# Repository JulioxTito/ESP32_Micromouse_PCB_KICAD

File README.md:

# ESP32-S3 Micromouse Robot Controller

A compact robotics breakout and control PCB designed for an autonomous maze-solving Micromouse robot. The board integrates power regulation, dual distance sensor interfaces, and motor driver breakouts around an ESP32-S3 system.

## Features

- **ESP32-S3 Core Module**
  - Surface-mount ESP32-S3-WROOM-1 footprint with dedicated antenna keep-out area
  - Native USB D+/D- lines routed to GPIO 19 and 20 for firmware flashing and debugging

- **Dual I2C Distance Sensor Breakouts**
  - Dual 4-pin headers (J3, J4) for left and right Time-of-Flight / IR obstacle sensors
  - Integrated 4.7k pull-up resistors on SDA and SCL lines

- **Dual DC Motor Driver Interface**
  - 6-pin header (J2) providing 5V, GND, dual PWM speed channels, and direction pins for an external H-bridge

- **USB-C Power Input & 3.3V Regulation**
  - 16-pin USB Type-C receptacle with dual 5.1k CC pull-down resistors for standard 5V supply
  - Onboard AMS1117-3.3 linear regulator with 10uF input/output ceramic filtering capacitors

- **Hardware Control Switches**
  - Tactile pushbuttons for RESET and BOOT mode selection with RC filtering and pull-ups

- **Chassis Mounting**
  - 4x M2.5 screw mounting holes with dedicated copper clearance for robot mechanical framing

## Schematic & Layout

Schematic:

[Download Schematic PDF](Media/esp32_micromouse_schematic.pdf)

PCB Layout:

## Skills Demonstrated

- KiCad 10 schematic capture and 2-layer PCB layout routing
- Complete Design Rule Check (DRC) verification with 0 errors and 0 parity warnings
- SMT footprint routing (ESP32-S3, USB-C, 0805 passives, SOT-223)
- Continuous ground plane flooding and thermal relief connections
- Functional silkscreen documentation with circuit grouping outlines and header pinouts
- Fabrication data generation (RS-274X Gerbers, Excellon NC drill files)

## Key Components & Footprints

| Designator | Component | Footprint / Package | Function |
| :--- | :--- | :--- | :--- |
| U1 | AMS1117-3.3 | SOT-223 | 5V to 3.3V LDO regulator |
| U2 | ESP32-S3-WROOM-1 | SMD Module | Main system microcontroller |
| J1 | USB-C Receptacle | 16-Pin SMD | 5V power and USB data |
| J2 | Pin Header 1x06 | 2.54 mm Pitch TH | Motor driver interface |
| J3, J4 | Pin Header 1x04 | 2.54 mm Pitch TH | Left and right I2C distance sensors |
| SW1, SW2 | Tactile Switch | 6x6 mm Pushbutton | RESET and BOOT triggers |
| R1, R2 | 5.1k Resistor | 0805 SMD | USB-C CC line pull-downs |
| R3, R4 | 10k Resistor | 0805 SMD | EN and BOOT pull-up network |
| R5, R6 | 4.7k Resistor | 0805 SMD | I2C SDA and SCL bus pull-ups |
| C1, C2 | 10uF Capacitor | 0805 SMD | LDO input and output decoupling |
| C3, C4 | 0.1uF / 1uF Capacitor | 0805 SMD | Power rail filtering and reset debounce |

## File Formats

- Hardware_Files/ contains editable KiCad project, schematic, and board layout files
- Gerbers_Micromouse_v1.0.zip contains generated fabrication Gerber and drill files for PCB manufacturing
- 3D Models/ contains component 3D step and wrl models used for rendering
- Media/ contains board layouts, schematic exports, and 3D renders

## Author

Julio Tito  
Rutgers University – New Brunswick  
B.S. in Electrical and Computer Engineering

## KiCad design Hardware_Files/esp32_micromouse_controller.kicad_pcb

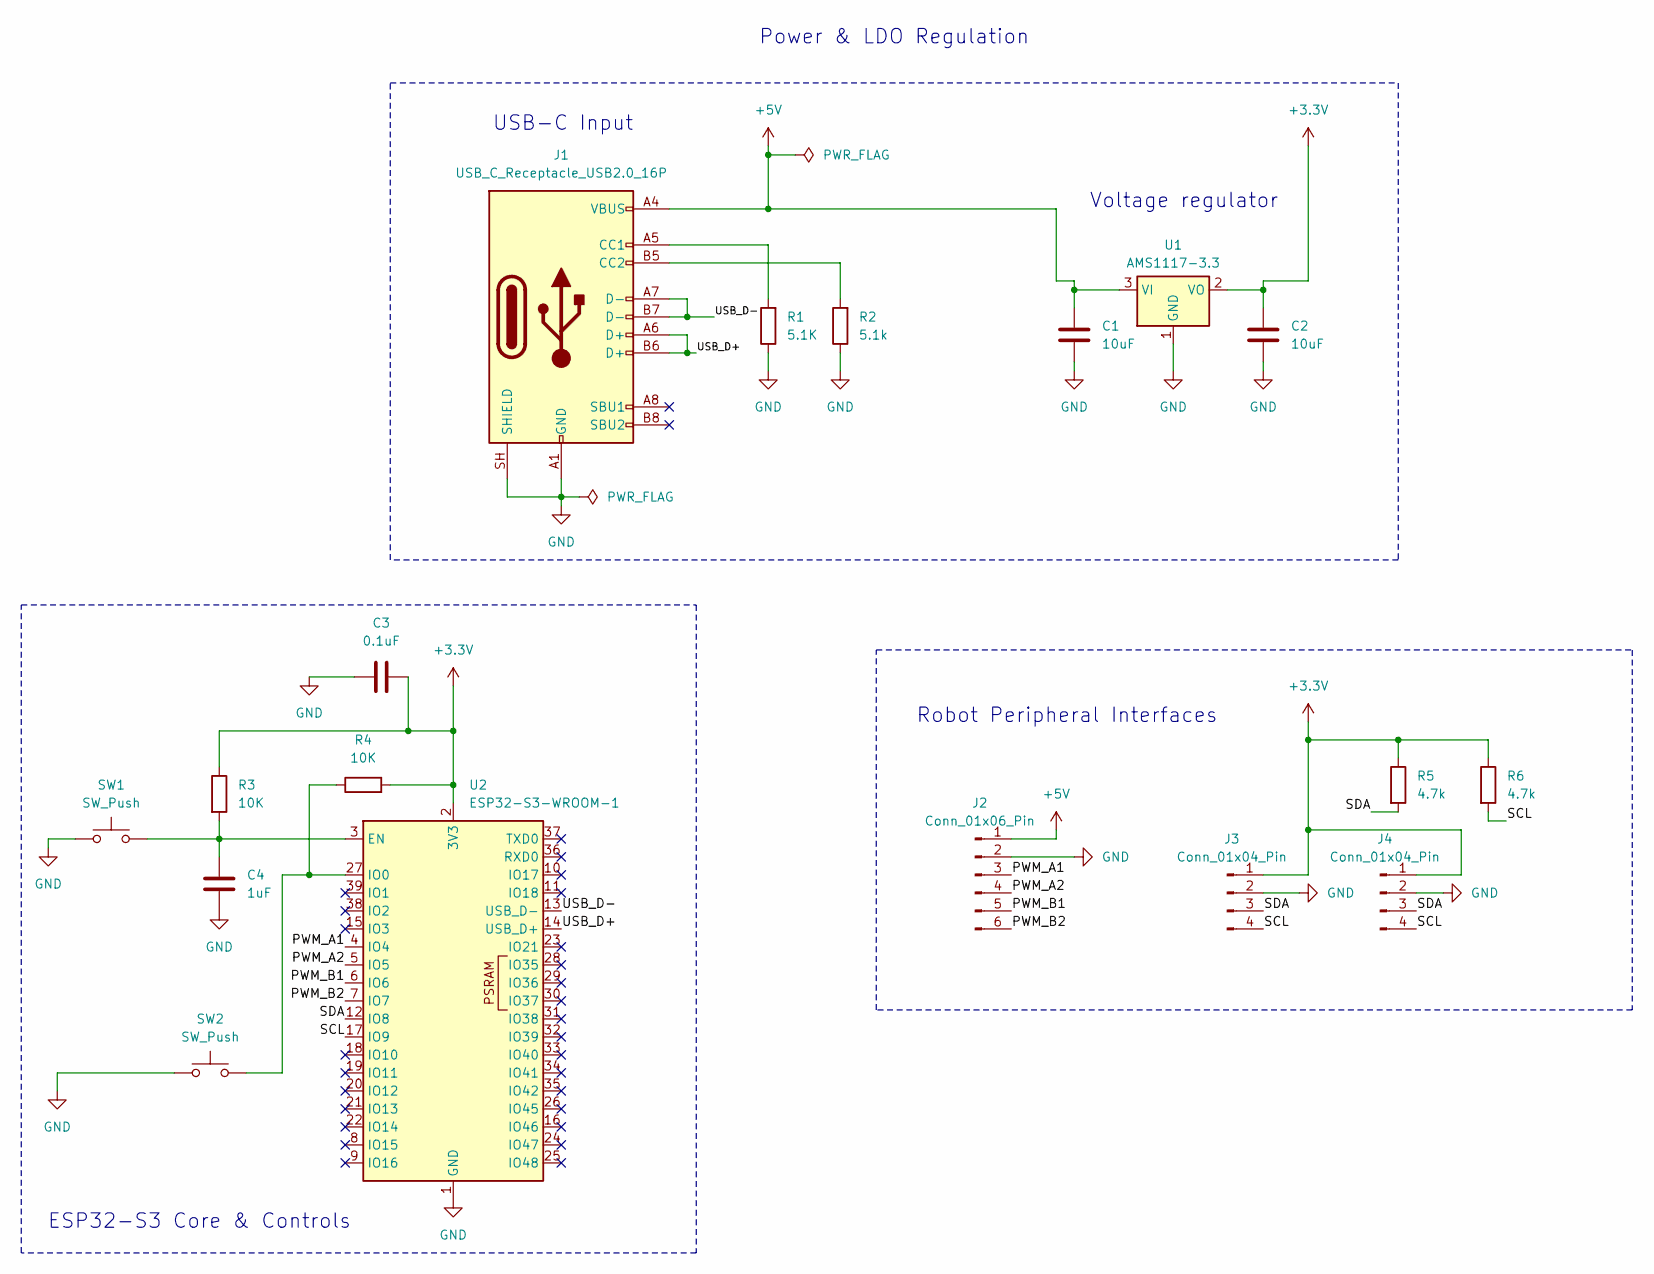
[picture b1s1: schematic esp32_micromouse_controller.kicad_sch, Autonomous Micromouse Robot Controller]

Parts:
C1, C2: 10uF; C_0805_2012Metric
C3: 0.1uF; C_0805_2012Metric
C4: 1uF; C_0805_2012Metric
J1: USB_C_Receptacle_USB2.0_16P; USB_C_Receptacle_HRO_TYPE-C-31-M-12
J2: Conn_01x06_Pin; PinHeader_1x06_P2.54mm_Vertical
J3, J4: Conn_01x04_Pin; PinHeader_1x04_P2.54mm_Vertical
R1: 5.1K; R_0805_2012Metric
R2: 5.1k; R_0805_2012Metric
R3, R4: 10K; R_0805_2012Metric
R5, R6: 4.7k; R_0805_2012Metric
SW1, SW2: SW_Push; SW_PUSH_6mm
U1: AMS1117-3.3; SOT-223-3_TabPin2
U2: ESP32-S3-WROOM-1

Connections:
+3.3V: C2.1, C3.1, J3.1, J4.1, R3.1, R4.2, R5.1, R6.1, U1.2 (VO), U2.2 (3V3)
+5V: C1.1, J1.A4 (VBUS), J1.A9 (VBUS), J1.B4 (VBUS), J1.B9 (VBUS), J2.1, U1.3 (VI)
/PWM_A1: J2.3, U2.4 (IO4)
/PWM_A2: J2.4, U2.5 (IO5)
/PWM_B1: J2.5, U2.6 (IO6)
/PWM_B2: J2.6, U2.7 (IO7)
/SCL: J3.4, J4.4, R6.2, U2.17 (IO9)
/SDA: J3.3, J4.3, R5.2, U2.12 (IO8)
/USB_D+: J1.A6 (D+), J1.B6 (D+), U2.14 (USB_D+)
/USB_D-: J1.A7 (D-), J1.B7 (D-), U2.13 (USB_D-)
GND: C1.2, C2.2, C3.2, C4.2, J1.A1 (GND), J1.A12 (GND), J1.B1 (GND), J1.B12 (GND), J1.SH (SHIELD), J2.2, J3.2, J4.2, R1.1, R2.1, SW1.1, SW2.1, U1.1 (GND), U2.1 (GND), U2.40 (GND), U2.41 (GND)
unnamed: J1.A5 (CC1), R1.2
unnamed: J1.B5 (CC2), R2.2
unnamed: C4.1, R3.2, SW1.2, U2.3 (EN)
unnamed: R4.1, SW2.2, U2.27 (IO0)

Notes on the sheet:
Power & LDO Regulation
ESP32-S3 Core & Controls
USB-C Input
Robot Peripheral Interfaces
Voltage regulator

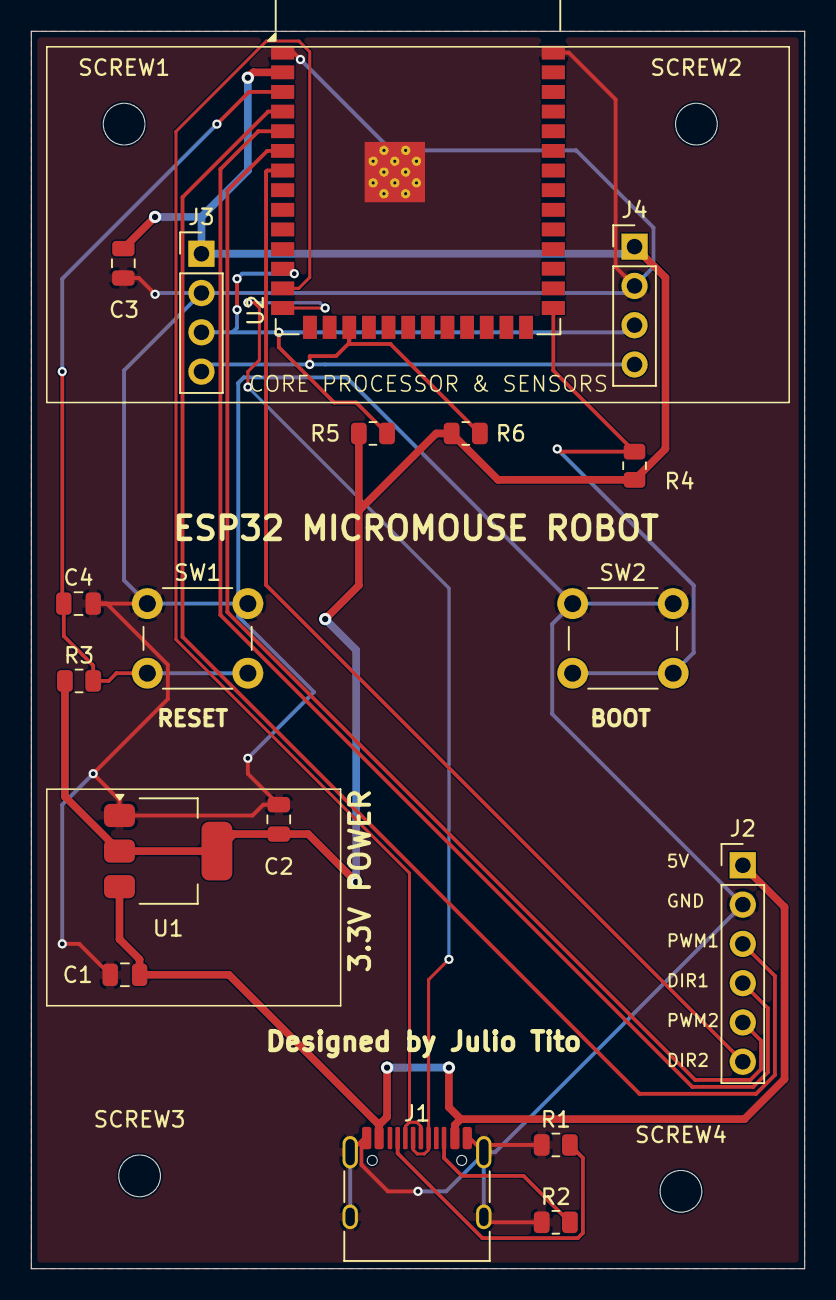
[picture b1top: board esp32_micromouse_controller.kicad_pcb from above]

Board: 2 copper layers, 50.0 x 80.0 mm, 22 parts (0 on the bottom side), 15 nets.

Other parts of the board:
SCREW1, SCREW2, SCREW3, SCREW4: MountingHole_2.7mm_M2.5
